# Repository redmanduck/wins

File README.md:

# Wi-Fi Indoor Navigation System 

GPS is the standard for navigation in embedded electronics today, but GPS signals are largely incapable of penetrating structures and providing an accurate or functional navigation system for indoor use. The Indoor Navigation System project is an attempt to address this issue, by combining multiple sensor techniques together to provide an accurate means of navigating an object indoors.

[]

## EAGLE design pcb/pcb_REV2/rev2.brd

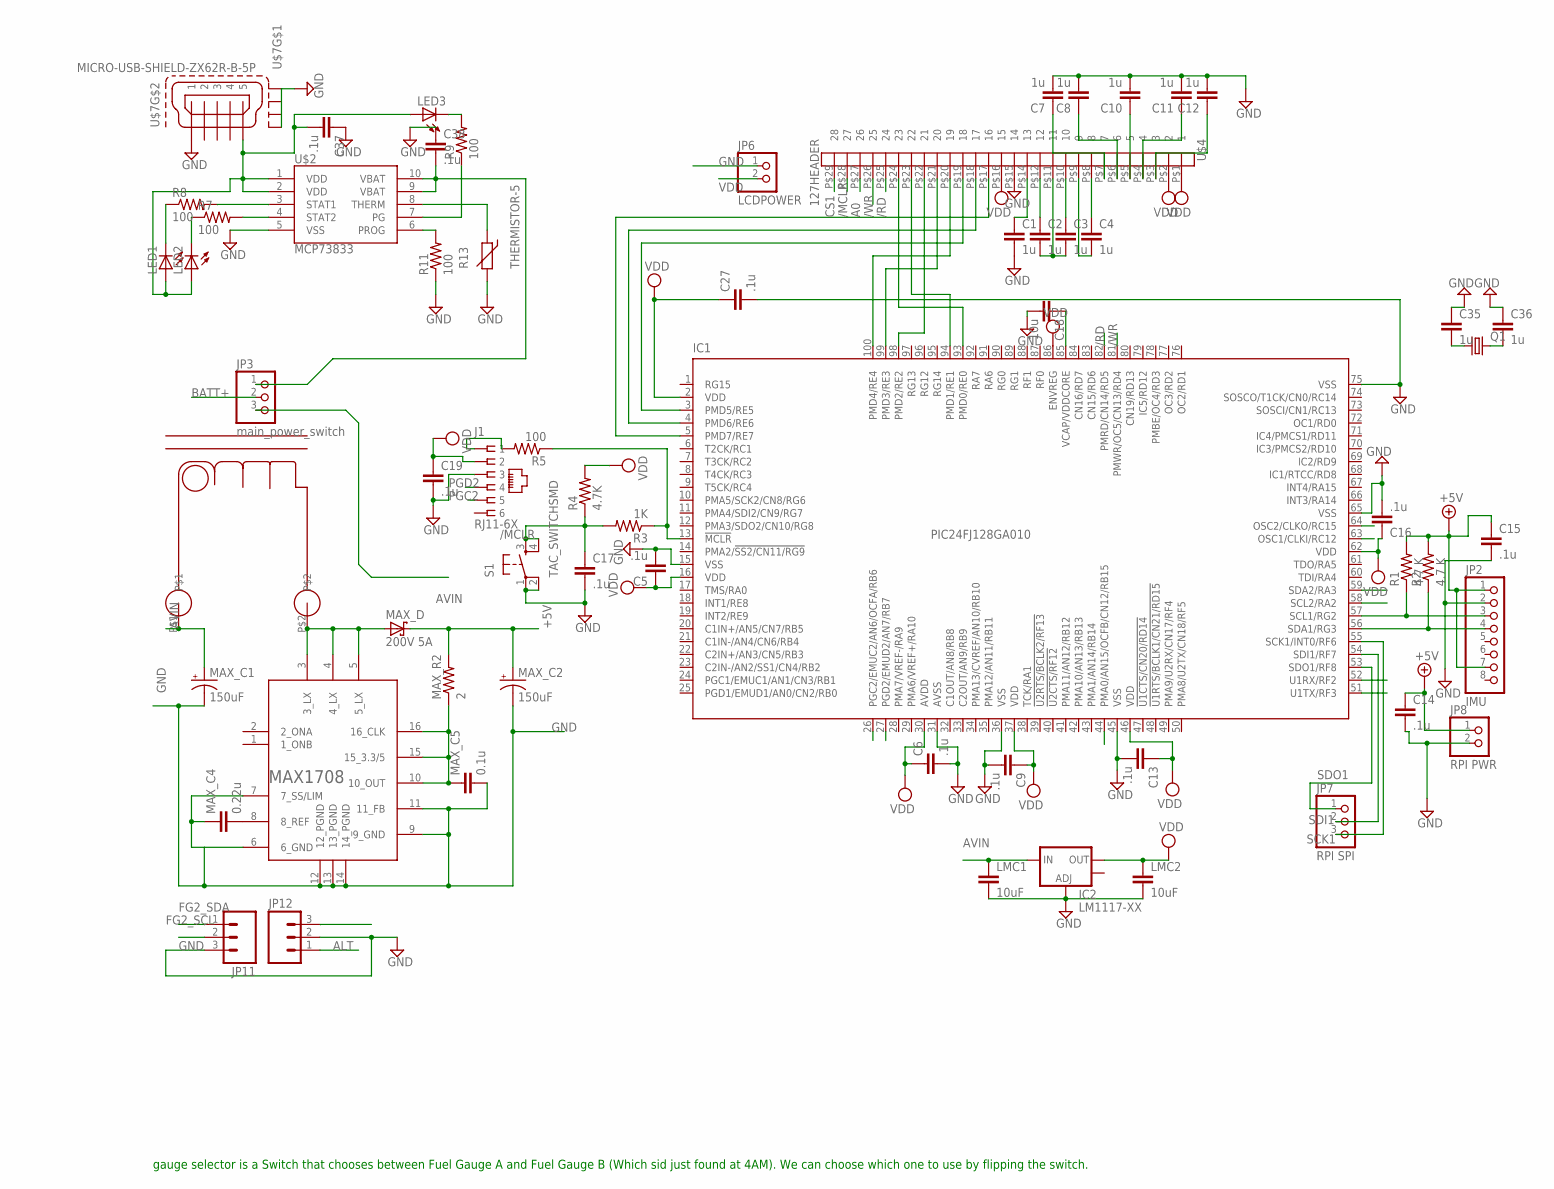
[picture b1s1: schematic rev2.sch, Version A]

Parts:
C1, C2, C3, C4, C7, C8, C10, C11, C12, C35, C36: 1u; C1206
C5, C6, C9, C13, C14, C15, C16, C17, C19, C27, C37, C38: .1u; C1206
C18: 10u; C1206
IC1: PIC24FJ128GA010; TQFP100-14X14
IC2: LM1117-XX; SOT223
J1: RJ11-6X; RJ11-NO_SHIELD
JP2: IMU; 1X08
JP3: main_power_switch; 1X03
JP6: LCDPOWER; 1X02
JP7: RPI SPI; 1X03
JP8: RPI PWR; 1X02
JP11, JP12: M03PTH; 1X03
LED1, LED2, LED3: LEDSMT1206; 1206
LMC1, LMC2: 10uF; C1206
MAX_C1, MAX_C2: 150uF; CT7343
MAX_C4: 0.22u; C1206
MAX_C5: 0.1u; C1206
MAX_D: 200V 5A; SMC
MAX_R2: 2; R1206
Q1: CRYTALHC49U-V; HC49U-V
R1, R2: 4.7 K; R1206
R3: 1K; R1206
R4: 4.7K; R1206
R5, R7, R8, R9, R11: 100; R1206
R13: THERMISTOR-5; R-5
S1: TAC_SWITCHSMD; TACTILE-SWITCH-SMD
U$2: MCP73833; MSOP10
U$3: MAX1708; QSOP16
U$4: 127HEADER; 1.27HEADER
U$6: UP2B-2R2-R
U$7: MICRO-USB-SHIELD-ZX62R-B-5P; ZX62R-B-5P

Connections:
+5V: C14.1, C15.1, JP2.1, JP2.7, JP8.1, MAX_C2.+, MAX_D.C, MAX_R2.2, R1.2, R2.2
/MCLR: C17.1, R3.2, R4.1, S1.3, S1.4, U$4.P$28 (27)
/RD: IC1.82 (PMRD/CN14/RD5), U$4.P$25 (24)
/WR: IC1.81 (PMWR/OC5/CN13/RD4), U$4.P$26 (25)
A0: IC1.44 (PMA0/AN15/OCFB/CN12/RB15), U$4.P$27 (26)
ALT: JP12.1
AVIN: IC2.3 (IN), JP3.3, LMC1.1, MAX_C1.+, U$6.P$1
BATT+: JP3.2, JP12.3
CS1: U$4.P$29 (28)
DS_DATA: IC1.52 (U1RX/RF2)
FG2_SCL: IC1.58 (SCL2/RA2), JP11.2
FG2_SDA: IC1.59 (SDA2/RA3), JP11.1
GND: C1.2, C5.2, C6.2, C7.2, C8.2, C9.2, C10.2, C11.2, C12.2, C13.2, C14.2, C15.2, C16.2, C17.2, C18.2, C19.2, C27.2, C35.1, C36.1, C37.1, C38.1, IC1.15 (VSS), IC1.31 (AVSS), IC1.36 (VSS), IC1.45 (VSS), IC1.65 (VSS), IC1.75 (VSS), IC2.1 (ADJ), J1.3, JP2.2, JP6.1, JP8.2, JP11.3, JP12.2, LMC1.2, LMC2.2, MAX_C1.-, MAX_C2.-, MAX_C4.1, MAX_C5.2, R11.1, R13.2, S1.1, S1.2, U$2.5 (VSS), U$3.6 (6_GND), U$3.7 (7_SS/LIM), U$3.9 (9_GND), U$3.11 (11_FB), U$3.12 (12_PGND), U$3.13 (13_PGND), U$3.14 (14_PGND), U$4.P$15 (14), U$7.1, U$7.M1 (S1), U$7.M2 (S2), U$7.M3 (S3), U$7.M4 (S4)
unnamed: IC1.57 (SCL1/RG2), JP2.3, R1.1
unnamed: IC1.56 (SDA1/RG3), JP2.4, R2.1
unnamed: LED1.C, R8.1
unnamed: IC1.13 (!MCLR), R3.1, R5.1
unnamed: R8.2, U$2.3 (STAT1)
unnamed: R7.2, U$2.4 (STAT2)
unnamed: C18.1, IC1.85 (VCAP/VDDCORE)
unnamed: IC1.5 (PMD7/RE7), U$4.P$17 (16)
unnamed: IC1.4 (PMD6/RE6), U$4.P$18 (17)
unnamed: IC1.3 (PMD5/RE5), U$4.P$19 (18)
unnamed: IC1.100 (PMD4/RE4), U$4.P$20 (19)
unnamed: IC1.99 (PMD3/RE3), U$4.P$21 (20)
unnamed: IC1.98 (PMD2/RE2), U$4.P$22 (21)
unnamed: IC1.94 (PMD1/RE1), U$4.P$23 (22)
unnamed: IC1.93 (PMD0/RE0), U$4.P$24 (23)
unnamed: C7.1, U$4.P$7 (7)
unnamed: C3.1, U$4.P$10 (10)
unnamed: LED2.C, R7.1
unnamed: C2.1, U$4.P$12 (12)
unnamed: C2.2, C3.2, U$4.P$11 (11)
unnamed: C1.1, U$4.P$14 (13)
unnamed: C4.2, U$4.P$9 (9)
unnamed: C4.1, U$4.P$8 (8)
unnamed: C8.1, U$4.P$6 (6)
unnamed: C10.1, U$4.P$5 (5)
unnamed: C11.1, U$4.P$4 (4)
unnamed: C12.1, U$4.P$3 (3)
unnamed: R9.1, U$2.7 (PG)
unnamed: J1.1, R5.2
unnamed: LED3.C, R9.2
unnamed: R11.2, U$2.6 (PROG)
unnamed: R13.1, U$2.8 (THERM)
unnamed: MAX_D.A, U$3.3 (3_LX), U$3.4 (4_LX), U$3.5 (5_LX), U$6.P$2
unnamed: MAX_C5.1, MAX_R2.1, U$3.10 (10_OUT), U$3.15 (15_3.3/5), U$3.16 (16_CLK)
unnamed: MAX_C4.2, U$3.8 (8_REF)
unnamed: C38.2, JP3.1, U$2.9 (VBAT), U$2.10 (VBAT)
OSC1: C36.2, IC1.63 (OSC1/CLKI/RC12), Q1.2
OSC2: C35.2, IC1.64 (OSC2/CLKO/RC15), Q1.1
PGC2: IC1.26 (PGC2/EMUC2/AN6/OCFA/RB6), J1.5
PGD2: IC1.27 (PGD2/EMUD2/AN7/RB7), J1.4
PIO: IC1.51 (U1TX/RF3)
SCK1: IC1.55 (SCK1/INT0/RF6), JP7.3
SDI1: IC1.54 (SDI1/RF7), JP7.2
SDO1: IC1.53 (SDO1/RF8), JP7.1
VDD: C5.1, C6.1, C9.1, C13.1, C16.1, C19.1, C27.1, IC1.2 (VDD), IC1.16 (VDD), IC1.30 (AVDD), IC1.37 (VDD), IC1.46 (VDD), IC1.62 (VDD), IC1.86 (ENVREG), IC2.2 (OUT), J1.2, JP6.2, LMC2.1, R4.2, U$4.P$1 (1), U$4.P$2 (2), U$4.P$16 (15)
VDDUSB: C37.2, LED1.A, LED2.A, LED3.A, U$2.1 (VDD), U$2.2 (VDD), U$7.5

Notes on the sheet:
gauge selector is a Switch that chooses between Fuel Gauge A and Fuel Gauge B (Which sid just found at 4AM). We can choose which one to use by flipping the switch.

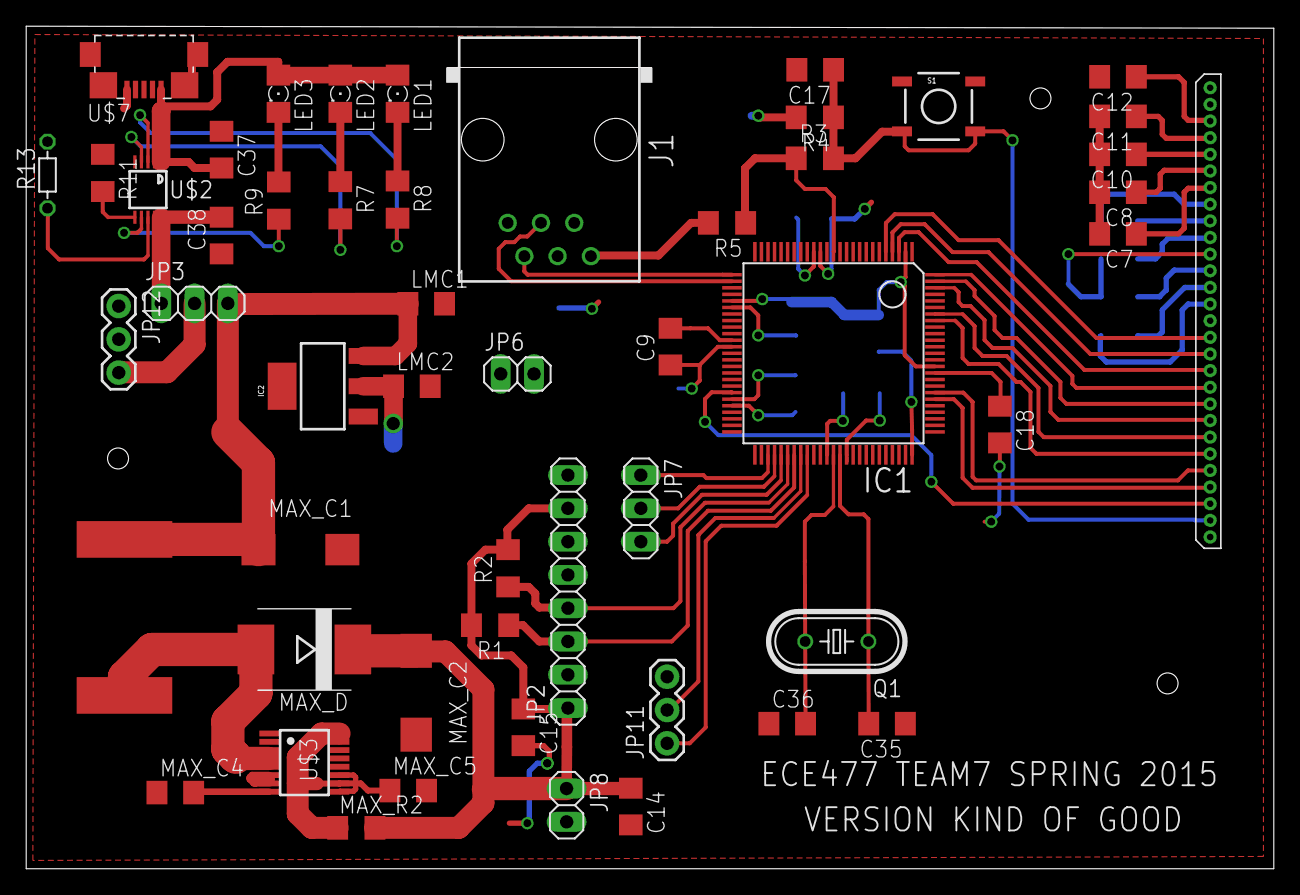
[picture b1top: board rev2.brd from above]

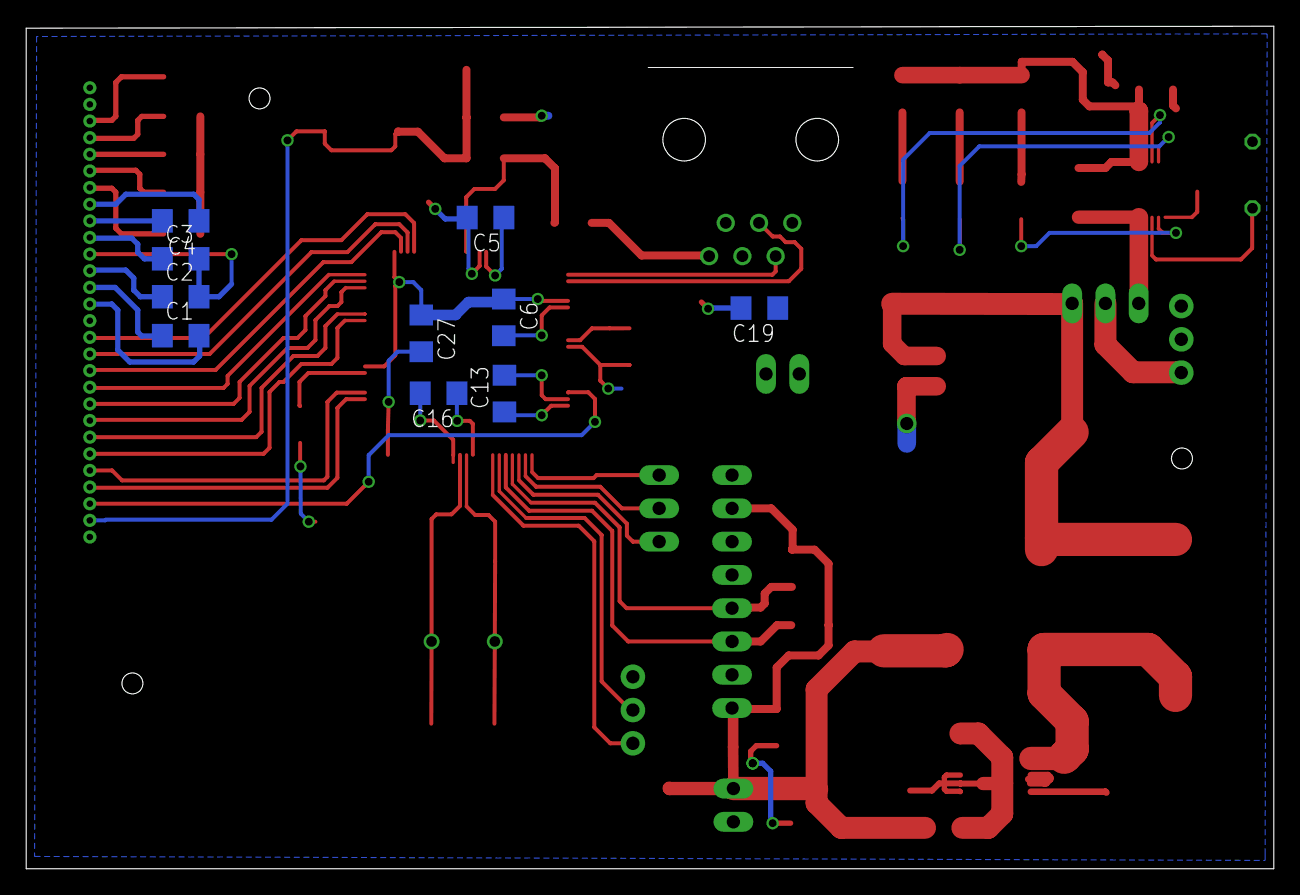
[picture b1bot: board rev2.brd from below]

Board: 2 copper layers, 95.2 x 64.3 mm, 62 parts (10 on the bottom side), 55 nets.

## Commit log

2015-01-23 Analysis files added
2015-01-23 Longer run continuous run data added
2015-01-25 Analysis script corrected, new data analyzed
2015-02-04 SPI testing
2015-02-04 PIC Dir
2015-02-05 C++ port
2015-02-06 WINSd daemon
2015-02-06 Stuff
2015-02-10 Localization algorithms added
2015-02-10 Serialization added with cereal
2015-02-11 yeah yea
2015-02-11 Integrate kdtree with map
2015-02-15 Sample.json added, kd tree integrated
2015-02-15 Example JSON extended
2015-02-20 Preliminary Mahalanobis localization working
2015-02-21 + Mahalobis distance estimation : added chi squared prob variant + Unique_ptr based memory system implemented
2015-02-24 Wifi scan
2015-02-26 rasp
2015-02-26 Implemented Kalman Filter and IMU data analysis
2015-02-26 Integrated Wifi scanning code
2015-02-26 Added missing files
2015-03-11 Version in design review
2015-03-13 Rev2
2015-03-13 Schem
2015-03-13 Kenzhebalin
2015-03-13 MAX1708 schem
2015-03-13 version one done
2015-03-13 go duck
2015-03-14 VERSION 1 with everything
2015-03-14 VERSION UNRELIABLE
2015-03-22 latest
2015-03-23 added lcd folder with ST7565 files
2015-03-24 Wifi localization default algorithm changed
2015-03-25 asdfa
2015-03-25 Added and updated PIC projects folders
2015-03-25 Incomplete changes: main, localization, spi, display, navigation
2015-03-25 Incomplete main code
2015-03-25 Test co
2015-03-25 Compile errors fixed
2015-03-25 Warning fixed
2015-03-26 Added mising spi_manager.cpp file
2015-03-26 Deleted platform dependant files
2015-03-27 Navigation complete
2015-03-27 Netbean project test
2015-03-28 Alright
2015-03-28 レーゴウ
2015-03-28 Cool Line things
2015-03-28 draw Circle
2015-03-28 draw Rect
2015-03-28 Bitmap Export for debugging
2015-03-28 Added glcdthing
2015-03-29 Add the ST thingy
2015-03-29 drawing using ST7565 now output bitmap file for debugging
2015-03-29 menu
2015-03-29 WiFi fine tuning
2015-03-30 WiFi analysis scripts added
2015-03-30 Errors in test fixed
2015-03-30 WiFi variant fix:
2015-03-31 Fine tune script correctins
2015-03-31 Keypad with debounce
2015-03-31 Keypad without integrated
2015-03-31 I see stagedDaulet
2015-03-31 More WiFi script fixes
2015-04-01 -Keypad and Display integrated
2015-04-03 Location combine code added Missing header global.h added
2015-04-03 pain in the ass wifi
2015-04-03 Boot and Shutdown test added
2015-04-03 Scan with TTL yea yea
2015-04-03 Clean Shutdown partly working
2015-04-07 iOkw
2015-04-08 updated pic folder, no changes in pcb_REV2 should be done
2015-04-08 updated pic with fixed spi communication between pic and pi
2015-04-08 Updated PIC. working SPI interface. battery levels on I2C2. IMU on I2C1
2015-04-10 Moved files
2015-04-10 Test
2015-04-10 Added test file for display.cpp
2015-04-10 dsplay
2015-04-10 testbuf
2015-04-10 duck
2015-04-10 iupdated ST7565 pagemap and startbyteswq q
2015-04-10 Hey duck
2015-04-10 Added offset byte
2015-04-10 Display on terminal implementation
2015-04-10 Fixed compile errors
2015-04-10 Added kalman.cpp
2015-04-10 Sid: Added scan data collected from the Pi!
2015-04-10 Replaced prints with logging
2015-04-11 Re-organized
2015-04-12 Chi sqaured WiFi algorithm fix
2015-04-12 Analsysis algorithm fix
2015-04-12 Pi data parsed, analysis script updated
2015-04-12 best parameters variance check added
2015-04-12 map data bug fix
2015-04-12 Added log scale data
2015-04-12 Forward and reverse runs combined
2015-04-12 dkenzheb
2015-04-12 save daemon
2015-04-13 map scaler almost working
2015-04-13 Algorithm version 2
2015-04-13 More WiFi experiments
2015-04-13 Top level kalman filter Q and R added, clean up
2015-04-14 WiFi with Kalman filter testing
2015-04-14 Top level Kalman filter done(?)
2015-04-15 iDaulet Kenzhealin
2015-04-15 Wifi tests, display lock added
2015-04-15 Wifi
2015-04-15 Peter ye
2015-04-15 should fix stuff
2015-04-15 Compilation okay
2015-04-15 instance stuff and copy mutex stuff
2015-04-15 Started working on Kenzhebalin Protocol
2015-04-15 Add travis
2015-04-15 iRemoved tab
2015-04-15 std11
2015-04-15 iSudo
2015-04-15 iTravis
2015-04-15 directory
2015-04-15 iShould fix it
2015-04-15 correct directory
2015-04-15 Static bug thingy
2015-04-15 Use G++x
2015-04-15 i--version
2015-04-15 Inspire
2015-04-15 Navigation module fixed
2015-04-15 "Missing bracket added"
2015-04-15 Prints added
2015-04-15 Navigation refined
2015-04-15 some update, imu does not work
2015-04-15 Kenzhebalin SPI protocol implemented
2015-04-15 renamed
2015-04-15 scaling should be correct
2015-04-16 WINS Map Assembly Instruction for Path AB
2015-04-16 Super imposed map
2015-04-16 Test change author name
2015-04-16 Test again
2015-04-17 LATEST PIC with all the projects PIC working is the latest project
2015-04-17 IMU Calibrating added
2015-04-17 Bug fixes
2015-04-17 Daemon changes
2015-04-18 iwlibtest added
2015-04-18 Correct maybe
2015-04-19 Pat's caching filter integrated
2015-04-19 Compile error fixed
2015-04-19 Bug fixes...
2015-04-19 Bg map clean
2015-04-19 Mapping code started
2015-04-19 More fixes
2015-04-19 Dont quit if scan failed
2015-04-19 Added lost n found files
2015-04-19 Bug fixes in wifiscan
2015-04-19 DMP stuff
2015-04-19 Updated PIC folder
2015-04-19 New monitor.cpp with I2c DMP
2015-04-20 DMP code and LCD is updated very fast
2015-04-20 WiFi navigation "kinda good"
2015-04-20 Display fxies
2015-04-21 some header
2015-04-24 updated monitor..cppw
2015-04-24 monitor updated
2015-04-24 SPI integrated
2015-04-24 Calibration added
2015-04-24 Logging enhanced
2015-04-24 Log filtering added
2015-04-24 Keypad fixed
2015-04-24 isave
2015-04-24 iDaemon added
2015-04-24 Kaypad ease of use
2015-04-27 Minor map thing
2015-04-27 World Map
2015-04-28 Fixed
2015-04-28 Not tested
2015-04-28 Main changed
2015-04-28 shutdown fixed
2015-04-28 Test loop made infinite
2015-04-29 Updated world, and display animaatie
2015-04-29 Display flipping thingy
2015-04-29 looks messed up
2015-04-29 Give me my file
2015-04-29 SImulator right side up
2015-04-29 gdb printers added
2015-04-29 Display fixed
2015-04-29 Blinking beacon
2015-04-30 Map shift and prevent weird
2015-04-30 very inefficient but politcally correct
2015-04-30 drawing to the back layer. Next: scaling
2015-04-30 Fixed byte order bug drawing
2015-04-30 Ready for scaling
2015-04-30 work in progress scanner
2015-04-30 Imu tuning code added
2015-04-30 Getscans, overall testing
2015-05-01 Should be ok
2015-05-01 imu, wifi analysis code added
2015-05-01 BMP parser
2015-05-01 World maker
2015-05-01 World changes
2015-05-01 Minor fixes
2015-05-01 Cofnirm press
2015-05-01 iWorlds
2015-05-01 Maybe this will fix ARM?
2015-05-01 data
2015-05-01 data analyzed
2015-05-01 maps added
2015-05-03 data and bug fixes
2015-05-04 bug fixes, analysis
2015-05-04 More data
2015-05-04 Trying to make wifi better
2015-05-04 Tuning
2015-05-04 Even more data
2015-05-04 Fixes
2015-05-04 Calibration fix
2015-05-04 Looks like everything's good
2015-05-04 nan fix
2015-05-04 compile fixes
2015-05-04 Disp
2015-05-04 Scale added
2015-05-05 Soviet Union
2015-05-05 template
2015-05-05 Daulet
2015-05-05 iyeah
2015-05-05 iadded balin
2015-05-06 dsiplay changes
2015-05-06 imu protection
2015-05-06 crash fix
2015-05-06 Should fix the shifting out of screen
2015-05-06 Navigation mode dash
2015-05-06 iFPsuhfuf
2015-05-06 imu optimization TEST
2015-05-07 Update README.md
    readme was outdated

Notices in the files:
parts and their libraries:
SparkFun-Retired: Licensing:Creative Commons ShareAlike 4.0 International - https://creativecommons.org/licenses/by-sa/4.0
